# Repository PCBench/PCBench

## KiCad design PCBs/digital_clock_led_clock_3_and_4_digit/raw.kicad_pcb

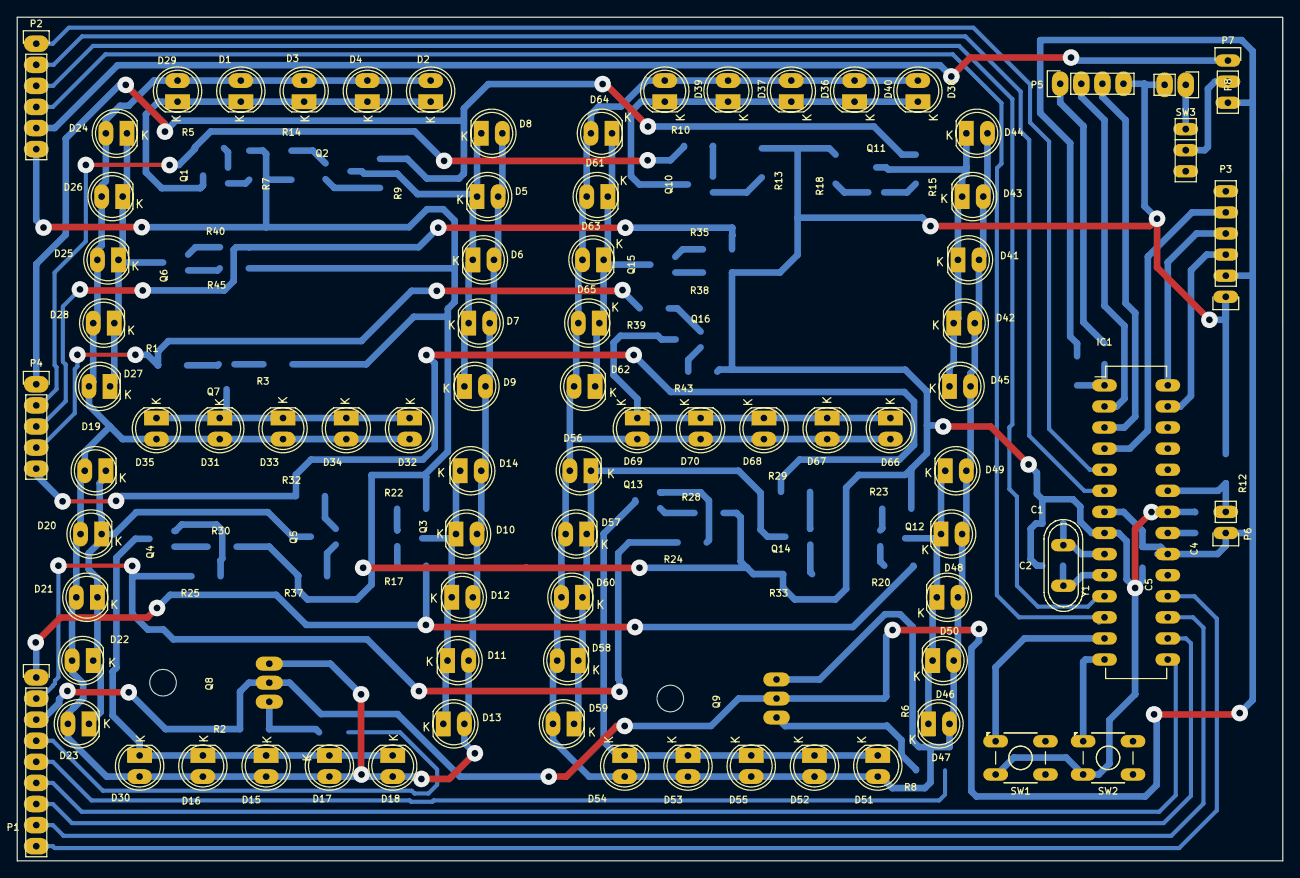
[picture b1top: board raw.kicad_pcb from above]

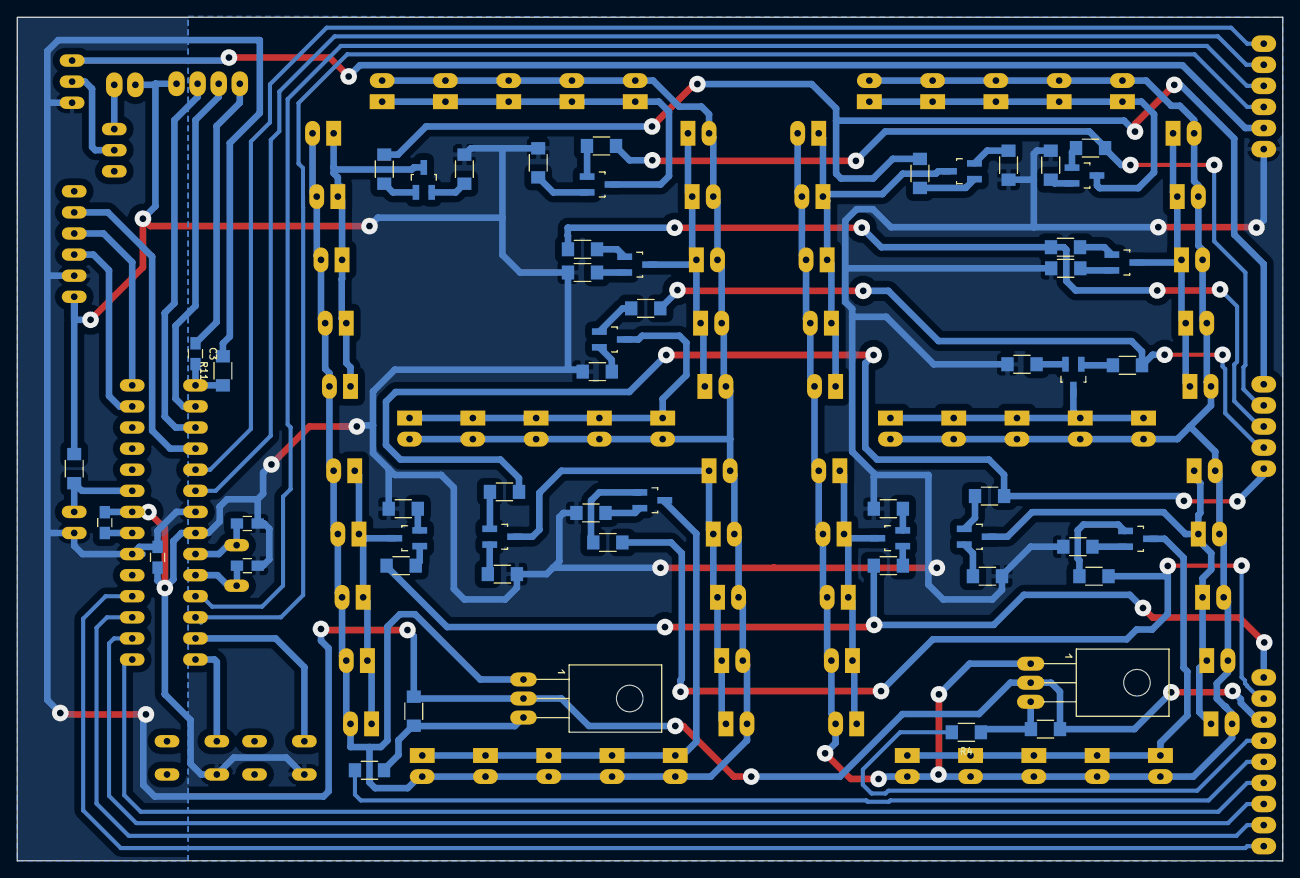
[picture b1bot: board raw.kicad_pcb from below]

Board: 2 copper layers, 152.4 x 101.6 mm, 138 parts (55 on the bottom side), 81 nets.

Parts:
C1, C2: 22P; C_0805_HandSoldering
C3, C4, C5: .1u; C_0805_HandSoldering
D1, D2, D3, D4, D15, D16, D17, D18, D29, D36, D37, D38, D39, D41, D42, D43, D44, D46, D47, D48, D49, D51, D52, D53, D54, D56, D57, D58, D59, D61, D62, D63, D64, D66, D67, D68, D69: D1_A; LED-5MM
D5, D6, D7, D8, D9, D10, D11, D12, D13, D14, D19, D20, D21, D22, D23, D24, D25, D26, D27, D28, D30, D31, D32, D33, D34, D35, D40, D45, D50, D55, D60, D65, D70: D1_B; LED-5MM
IC1: ATMEGA328P-P; DIP-28_W7.62mm_LongPads
P1: BOT_PINS; Pin_Header_Straight_1x09
P2: TOP_PINS; Pin_Header_Straight_1x06
P3: DS3231; Pin_Header_Straight_1x06
P4: CONN_01X05; Pin_Header_Straight_1x05
P5: ICSP; Pin_Header_Straight_1x04
P6: LDR; Pin_Header_Straight_1x02
P7: PWR_SEL; Pin_Header_Straight_1x03
P8: PWR_IN; Pin_Header_Straight_1x02
Q1, Q2, Q3, Q4, Q5, Q6, Q7, Q10, Q11, Q12, Q13, Q14, Q15, Q16: MMBT3904; SOT-23_Handsoldering
Q8, Q9: BD140; SOT126_SOT32_Housing_Horizontal
R1, R5, R9, R10, R15, R17, R20, R24, R25, R29, R32, R35, R39, R40: 560; R_1206_HandSoldering
R2, R6: 0; R_1206_HandSoldering
R3, R7, R13, R14, R18, R22, R23, R28, R30, R33, R37, R38, R43, R45: 68; R_1206_HandSoldering
R4, R8: 220; R_1206_HandSoldering
R11: 1K; R_1206_HandSoldering
R12: 10K; R_1206_HandSoldering
SW1: MENU; SW_TH_Tactile_Omron_B3F-10xx
SW2: UP; SW_TH_Tactile_Omron_B3F-10xx
SW3: Switch_SPDT_x2; SW_Micro_SPST
Y1: 16MHZ; Crystal_HC49-U_Vertical

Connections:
+5V: C5.2, IC1.7, IC1.20, P1.3, P3.2, P6.1, P7.3, Q8.2, Q9.2, R2.2, R6.2, R11.2
/D3_IN: P1.4, R4.2
/D4_IN: P1.5, R8.2
/SEG_A: P4.2, R5.2, R10.2
/SEG_B: P4.1, R9.2, R15.2
/SEG_C: P1.1, R17.2, R20.2
/SEG_D: P1.2, R24.2, R25.2
/SEG_E: P4.5, R29.2, R32.2
/SEG_F: P4.3, R35.2, R40.2
/SEG_G: P4.4, R1.2, R39.2
BCD_A: IC1.12, P2.4
BCD_B: IC1.5, P2.1
BCD_C: IC1.6, P2.2
BCD_D: IC1.11, P2.3
DIG_0: IC1.18, P1.9
DIG_1: IC1.17, P1.8
DIG_2: IC1.16, P1.7
GND: C1.2, C2.2, C4.2, C5.1, IC1.8, IC1.22, P2.6, P3.1, P5.4, P8.2, R3.2, R7.2, R12.2, R13.2, R14.2, R18.2, R22.2, R23.2, R28.2, R30.2, R33.2, R37.2, R38.2, R43.2, R45.2, SW1.2, SW2.2
KEY_MENU: IC1.14, SW2.1
KEY_UP: IC1.13, SW1.1
LDR: IC1.23, P6.2, R12.1
unnamed: C4.1, IC1.21
unnamed: D1.1, D2.1, D3.1, D4.1, D29.1, Q1.3
unnamed: D1.2, D2.2, D3.2, D4.2, D5.2, D6.2, D7.2, D8.2, D9.2, D10.2, D11.2, D12.2, D13.2, D14.2, D15.2, D16.2, D17.2, D18.2, D19.2, D20.2, D21.2, D22.2, D23.2, D24.2, D25.2, D26.2, D27.2, D28.2, D29.2, D30.2, D31.2, D32.2, D33.2, D34.2, D35.2, Q8.1
unnamed: D5.1, D6.1, D7.1, D8.1, D9.1, Q2.3
unnamed: D10.1, D11.1, D12.1, D13.1, D14.1, Q3.3
unnamed: D15.1, D16.1, D17.1, D18.1, D30.1, Q4.3
unnamed: D19.1, D20.1, D21.1, D22.1, D23.1, Q5.3
unnamed: D24.1, D25.1, D26.1, D27.1, D28.1, Q6.3
unnamed: D31.1, D32.1, D33.1, D34.1, D35.1, Q7.3
unnamed: D36.1, D37.1, D38.1, D39.1, D40.1, Q10.3
unnamed: D36.2, D37.2, D38.2, D39.2, D40.2, D41.2, D42.2, D43.2, D44.2, D45.2, D46.2, D47.2, D48.2, D49.2, D50.2, D51.2, D52.2, D53.2, D54.2, D55.2, D56.2, D57.2, D58.2, D59.2, D60.2, D61.2, D62.2, D63.2, D64.2, D65.2, D66.2, D67.2, D68.2, D69.2, D70.2, Q9.1
unnamed: D41.1, D42.1, D43.1, D44.1, D45.1, Q11.3
unnamed: D46.1, D47.1, D48.1, D49.1, D50.1, Q12.3
unnamed: D51.1, D52.1, D53.1, D54.1, D55.1, Q13.3
unnamed: D56.1, D57.1, D58.1, D59.1, D60.1, Q14.3
unnamed: D61.1, D62.1, D63.1, D64.1, D65.1, Q15.3
unnamed: D66.1, D67.1, D68.1, D69.1, D70.1, Q16.3
unnamed: Q1.1, R5.1
unnamed: Q1.2, R7.1
unnamed: Q2.1, R9.1
unnamed: Q2.2, R14.1
unnamed: Q3.1, R17.1
unnamed: Q3.2, R22.1
unnamed: Q4.1, R25.1
unnamed: Q4.2, R30.1
unnamed: Q5.1, R32.1
unnamed: Q5.2, R37.1
unnamed: Q6.1, R40.1
unnamed: Q6.2, R45.1
unnamed: Q7.1, R1.1
unnamed: Q7.2, R3.1
unnamed: Q8.3, R2.1, R4.1
unnamed: Q9.3, R6.1, R8.1
unnamed: Q10.1, R10.1
unnamed: Q10.2, R13.1
unnamed: Q11.1, R15.1
unnamed: Q11.2, R18.1
unnamed: Q12.1, R20.1
unnamed: Q12.2, R23.1
unnamed: Q13.1, R24.1
unnamed: Q13.2, R28.1
unnamed: Q14.1, R29.1
unnamed: Q14.2, R33.1
unnamed: Q15.1, R35.1
unnamed: Q15.2, R38.1
unnamed: Q16.1, R39.1
unnamed: Q16.2, R43.1
OSC1: C1.1, IC1.9, Y1.1
OSC2: C2.1, IC1.10, Y1.2
PWM: IC1.15, P1.6
RST: C3.1, P5.1
RX: IC1.2, P5.2
SCL: IC1.28, P3.4
SDA: IC1.27, P3.3
SQW: IC1.4, P3.5
TX: IC1.3, P5.3
VIN: P2.5, P7.1
VSUP: P8.1, SW3.1
VSUPPLY: P7.2, SW3.2
~RESET: C3.2, IC1.1, R11.1

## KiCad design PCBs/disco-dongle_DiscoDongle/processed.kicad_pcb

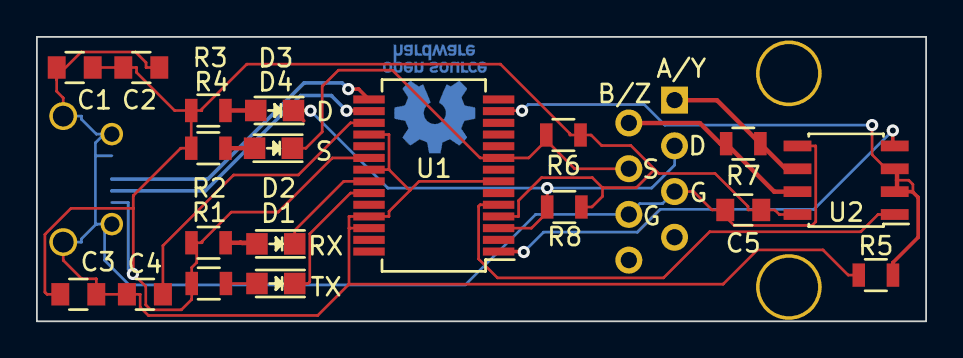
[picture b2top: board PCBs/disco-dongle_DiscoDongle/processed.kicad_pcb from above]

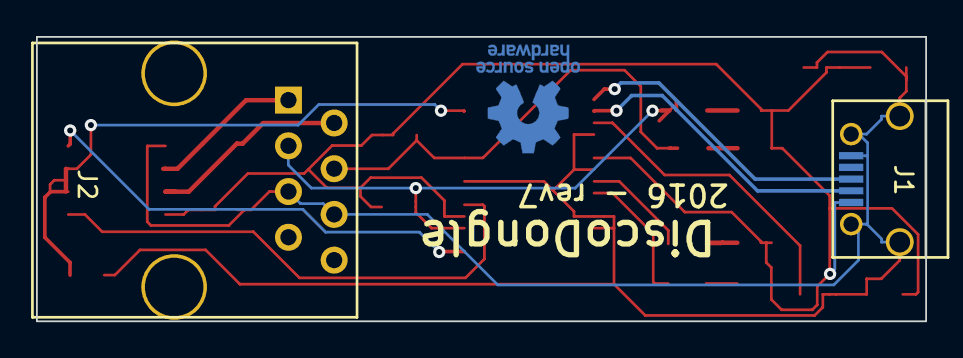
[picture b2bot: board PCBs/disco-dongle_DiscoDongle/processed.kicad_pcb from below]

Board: 2 copper layers, 49.4 x 15.8 mm, 21 parts (2 on the bottom side), 18 nets.

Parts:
C1, C4, C5: 100nF; C_0805
C2: 4.7uF; C_0805
C3: 10nF; C_0805
D1: TX; LED_0805
D2: RX; LED_0805
D3: Daisy; LED_0805
D4: Signal; LED_0805
J1: USB_B_Micro; USB_Micro-B
J2: RJ45; RJ45_8
R1, R2, R3, R4: 200; R_0805
R5, R6, R8: 20k; R_0805
R7: 120; R_0805
U1: FT232RL; SSOP-28_5.3x10.2mm_Pitch0.65mm
U2: ISL81487E; SOIC-8_3.9x4.9mm_Pitch1.27mm

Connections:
+5V: C1.1, C2.1, C3.1, C5.1, J1.1, R1.1, R2.1, R3.1, R4.1, R6.1, R8.1, U1.4, U1.20, U2.8
Daisy: D3.1, J2.3, R8.2, U1.3
GND: C1.2, C2.2, C3.2, C4.2, C5.2, J1.5, J1.6, J2.5, J2.6, R5.2, U1.7, U1.18, U1.21, U1.25, U1.26, U2.5
unnamed: C4.1, U1.17
unnamed: D1.2, R1.2
unnamed: D2.2, R2.2
unnamed: D3.2, R3.2
unnamed: D4.2, R4.2
unnamed: J1.2, U1.16
unnamed: J1.3, U1.15
unnamed: J2.1, R7.2, U2.6
unnamed: J2.2, R7.1, U2.7
unnamed: R5.1, U1.13, U2.2, U2.3
unnamed: U1.1, U2.4
unnamed: U1.5, U2.1
RXLED: D2.1, U1.22
Signal: D4.1, J2.4, R6.2, U1.9
TXLED: D1.1, U1.23

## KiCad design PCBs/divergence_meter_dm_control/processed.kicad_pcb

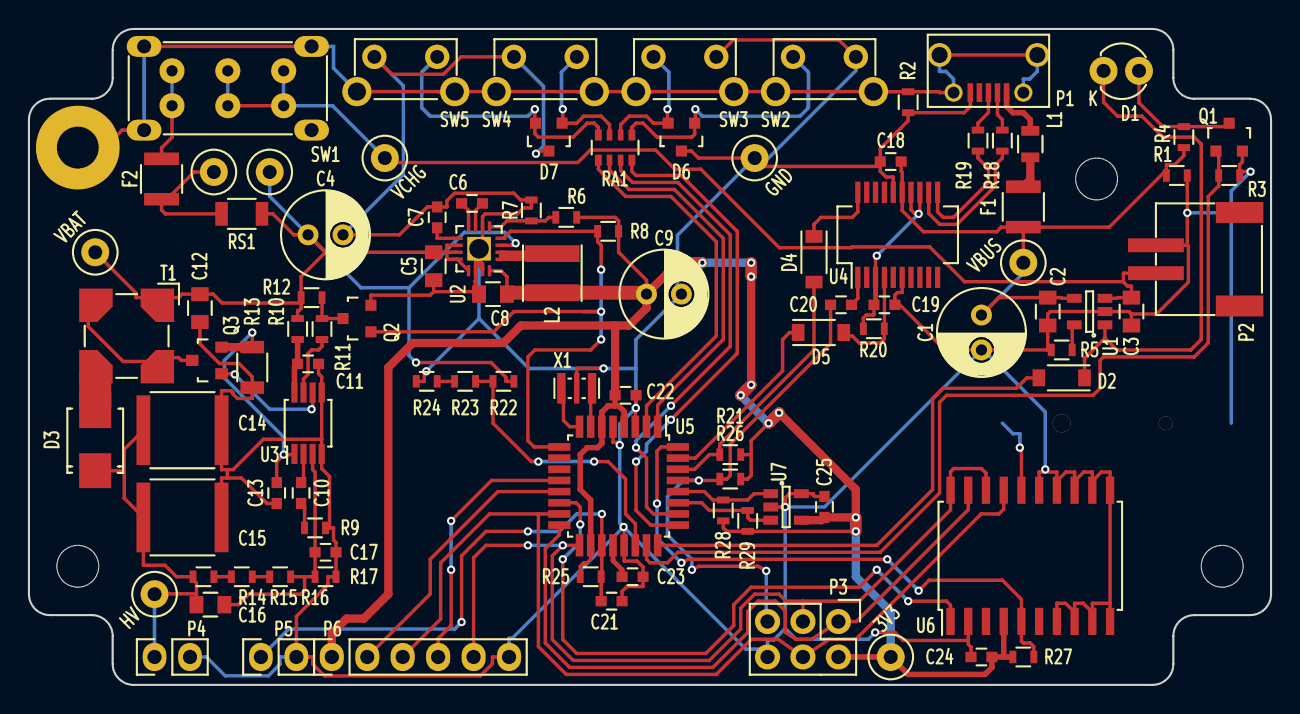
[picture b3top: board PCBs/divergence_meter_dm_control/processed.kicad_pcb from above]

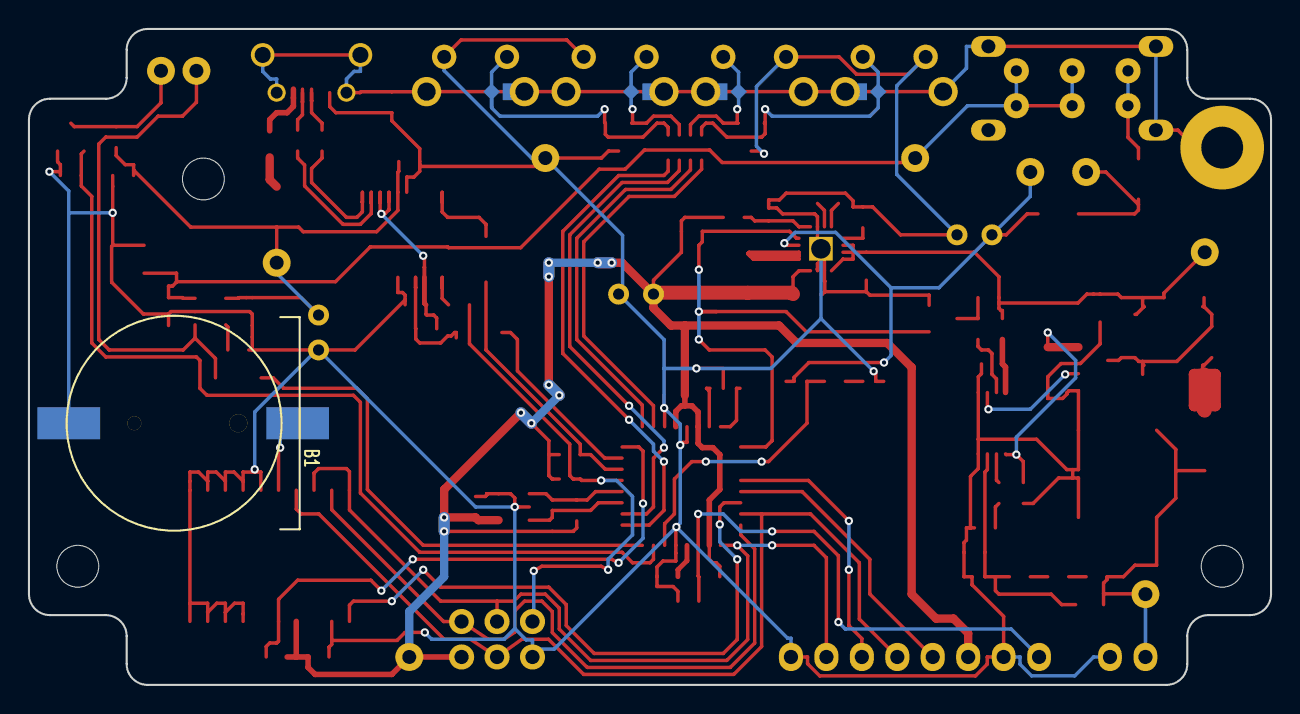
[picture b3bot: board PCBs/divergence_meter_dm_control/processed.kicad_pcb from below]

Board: 2 copper layers, 89.0 x 47.0 mm, 103 parts (5 on the bottom side), 69 nets.

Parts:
B1: Battery; Battery_CR1220
C1, C4, C9: 47u; C_Radial_D6.3_L11.2_P2.5
C2, C3: 4.7u; C_0805
C5, C8, C12: 22u; C_0805
C6, C7, C13, C17: 0.01u; C_0603
C10, C11, C18, C19, C20, C22, C23, C24, C25: 0.1u; C_0603
C14, C15: 1u; C_2220
C16: 100p; C_0805
C21: 1u; C_0603
D1: CHG; LED-3MM
D2, D4, D5: D_Small; SOD-123
D3: STPS4S200; SMB_Standard
D6, D7: MMBZ9V1ALT1G; SOT-23
F1, F2: 1.1A; R_1210
G1, G2, G3, G4: Jumper_NO_Small; SparkGap_0.2mm
L1: Ferrite; R_0805
L2: 1uH; Inductor_Taiyo-Yuden_NR-40xx
P1: USB_OTG; USB_Micro-B
P2: LiPo; Conn_S2B-PH-SM4-TB
P3: ISP; Pin_Header_Straight_2x03
P4: HV; Pin_Header_Straight_1x02
P5: OPTO; Pin_Header_Straight_1x02
P6: DATA; Pin_Header_Straight_1x06
Q1, Q2: 2N7002; SOT-23
Q3: RSR030N06TL; SOT-23
R1, R2, R16: 1M; R_0603
R3, R6: 470k; R_0603
R4, R9, R20, R21: 1k; R_0603
R5: 2k; R_0603
R7, R11: 150k; R_0603
R8, R22, R23, R24: 100k; R_0603
R10: 20; R_0603
R12, R26: 10k; R_0603
R13: 0.1; R_1206
R14: 24k; R_0603
R15: 820k; R_0603
R17: 13k; R_0603
R18, R19: 27; R_0603
R25: 47k; R_0603
R27, R28, R29: 4.7k; R_0603
RA1: 100; R_Array_Convex_4x0603
RS1: 0.01; R_1206
SW1: PWR; PINHEAD1-3
SW2, SW3, SW4, SW5: Push; SW_Tactile_SPST_Angled
T1: LPR6235; Transformer_LPR6235
TP1: VBUS; Test_1
TP2: VCHG; Test_1
TP3: VBAT; Test_1
TP4: 3.3V; Test_1
TP5: GND; Test_1
TP6: 170V; Test_1
TP7: RS1A; Test_1
TP8: RS1B; Test_1
U1: MCP73831; SOT-23-5
U2: TLV62090; QFN-16-1EP_3x3mm_Pitch0.5mm
U3: LM3478; MSOP-8_3x3mm_Pitch0.65mm
U4: FT231XS; SSOP-20_4.0x8.5mm_Pitch0.635mm
U5: ATMEGA328P-A; TQFP-32_7x7mm_Pitch0.8mm
U6: DS3234; SOIC-20W_7.5x12.8mm_Pitch1.27mm
U7: 24AA01T-I/OT; SOT-23-5
X1: 8MHz; Ceralock_CSTCE-G

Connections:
+3V3: C8.1, C9.1, C22.1, C24.1, C25.2, L2.2, P3.2, P6.1, R6.1, R8.1, R21.1, R25.1, R26.1, R27.1, R28.1, R29.1, TP4.1, U2.16, U5.4, U5.6, U5.18, U6.4, U7.4
/APWM: P6.2, U5.13
/AVR_RST: C20.1, P3.5, R26.2, U5.29
/CHASSIS: G1.2, G2.2, G3.2, G4.2, P1.6, R2.1, SW1.4, SW2.3, SW2.4, SW3.3, SW3.4, SW4.3, SW4.4, SW5.3, SW5.4
/CHG_LED: Q1.1, R3.1, U5.23
/CHG_STAT: D2.2, U5.24
/DS_SS: U5.14, U6.1
/FB: C16.2, C17.1, R16.2, R17.1, U3.3
/FT->AVR: D4.2, R21.2, U5.30
/FT<-AVR: D5.1, U5.31
/ISEN: C13.1, Q3.2, R13.1, U3.1
/MISO: P3.1, U5.16, U6.19
/MOSI: P3.4, P6.3, U5.15, U6.17
/OPTO: C21.1, P5.1, R25.2, U5.19
/PG: Q2.1, R8.2, U2.4, U5.9
/RCLK: P6.4, U5.12
/SCK: P3.3, P6.5, U5.17, U6.18, U6.20
/SCL: R28.2, U5.28, U7.1
/SDA: R29.2, U5.27, U7.3
/SQW: R27.2, U5.32, U6.5
/SW0: RA1.8, U5.25
/SW1: RA1.7, U5.26
/SW2: RA1.6, U5.1
/SW3: RA1.5, U5.2
/VBAT: C4.1, C5.1, C12.1, R10.1, R12.2, R22.1, RS1.2, T1.1, TP3.1, TP8.1, U2.3, U2.10, U2.11, U2.12, U2.13
/VBUS: C1.1, C2.1, C18.1, F1.2, R1.1, R4.1, TP1.1, U1.4, U4.15
/VCHG: C3.1, P2.1, SW1.1, SW1.2, TP2.1, U1.3
GND: B1.2, C1.2, C2.2, C3.2, C4.2, C5.2, C7.2, C8.2, C9.2, C11.2, C12.2, C13.2, C14.2, C15.2, C17.2, C18.2, C19.2, C21.2, C22.2, C23.2, C24.2, C25.1, D6.3, D7.3, P1.5, P2.2, P3.6, P4.2, P5.2, P6.6, Q1.2, Q2.2, R1.2, R2.2, R3.2, R5.2, R7.2, R9.2, R13.2, R17.2, R24.2, SW2.2, SW3.2, SW4.1, SW5.1, TP5.1, U1.2, U2.6, U2.14, U2.15, U3.4, U3.5, U4.6, U4.16, U5.3, U5.5, U5.21, U6.2, U6.7, U6.8, U6.9, U6.10, U6.11, U6.12, U6.13, U6.14, U6.15, U7.2, U7.5, X1.3
HT: C14.1, C15.1, C16.1, D3.1, P4.1, R14.1, TP6.1
unnamed: B1.1, U6.16
unnamed: C6.1, U2.8
unnamed: C6.2, U2.7
unnamed: C7.1, U2.9
unnamed: C10.1, U3.2
unnamed: C10.2, R9.1
unnamed: C11.1, R10.2, U3.8
unnamed: C19.1, R20.1, U4.3, U4.13, U4.14
unnamed: C20.2, U4.1
unnamed: C23.1, U5.20
unnamed: D1.1, D2.1, U1.1
unnamed: D1.2, Q1.3, R4.2
unnamed: D3.2, T1.3
unnamed: D4.1, U4.20
unnamed: D5.2, R20.2, U4.4
unnamed: D6.1, G1.1, RA1.1, SW2.1
unnamed: D6.2, G2.1, RA1.2, SW3.1
unnamed: D7.1, G3.1, RA1.3, SW4.2
unnamed: D7.2, G4.1, RA1.4, SW5.2
unnamed: F1.1, L1.2
unnamed: F2.1, SW1.3
unnamed: F2.2, RS1.1, TP7.1
unnamed: L1.1, P1.1
unnamed: L2.1, U2.1, U2.2
unnamed: P1.2, R18.1
unnamed: P1.3, R19.1
unnamed: Q2.3, R11.2, R12.1
unnamed: Q3.1, U3.6
unnamed: Q3.3, T1.2, T1.4
unnamed: R5.1, U1.5
unnamed: R6.2, R7.1, U2.5
unnamed: R11.1, U3.7
unnamed: R14.2, R15.1
unnamed: R15.2, R16.1
unnamed: R18.2, U4.12
unnamed: R19.2, U4.11
unnamed: R22.2, R23.1, U5.22
unnamed: R23.2, R24.1
unnamed: U5.7, X1.2
unnamed: U5.8, X1.1

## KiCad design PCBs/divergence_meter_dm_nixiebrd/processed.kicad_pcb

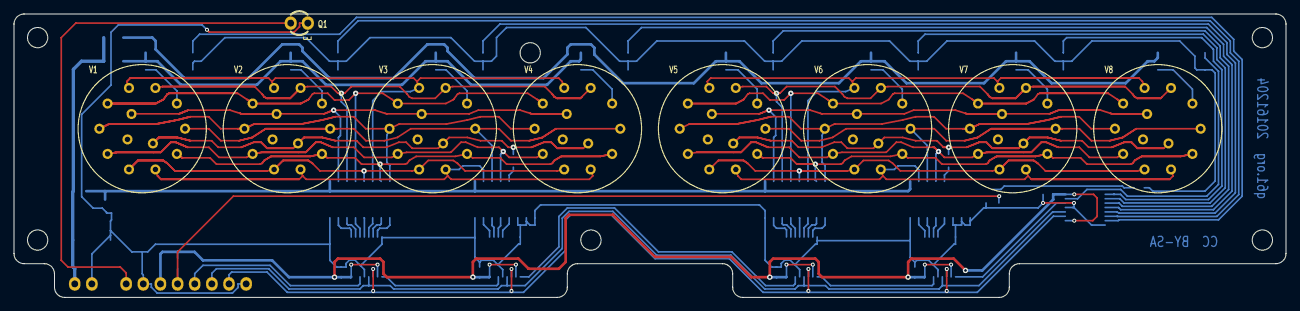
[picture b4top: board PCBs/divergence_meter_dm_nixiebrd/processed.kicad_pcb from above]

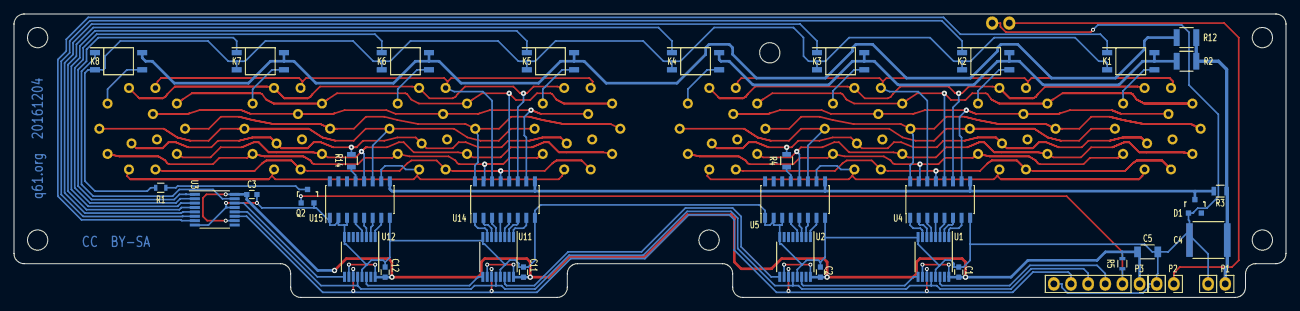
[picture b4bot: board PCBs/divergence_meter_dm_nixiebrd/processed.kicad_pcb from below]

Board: 2 copper layers, 188.5 x 42.0 mm, 45 parts (36 on the bottom side), 79 nets.

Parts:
C1, C2, C3, C11, C12: 0.1u; C_0603
C4: 1u250V; C_2220
C5: 10u; C_1206
D1: 75V_SOT23; SOT-23
K1, K2, K3, K4, K5, K6, K7, K8: TLP188; Optocoupler_SOP6_4
P1: HV; Pin_Header_Straight_1x02
P2: Opto; Pin_Header_Straight_1x02
P3: Signal; Pin_Header_Straight_1x06
Q1: OptTr; OptoTr_TH_3mm_Pitch2.54mm
Q2: 2N7002; SOT-23
R1: 470; R_0603
R2, R12: 3.3k; R_1210
R3: 220k; R_0805
R4, R14: 47k; R_0805
R5: 100k; R_0603
U1, U2, U3, U11, U12: 74HC595; TSSOP-16_4.4x5mm_Pitch0.65mm
U4, U5, U14, U15: SN75468; SOIC-16_3.9x9.9mm_Pitch1.27mm
V1, V2, V3, V4, V5, V6, V7, V8: NL-841; NL-902

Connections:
+3V3: C1.1, C2.1, C3.1, C5.1, C11.1, C12.1, P3.1, R5.1, U1.10, U1.16, U2.10, U2.16, U3.10, U3.16, U11.10, U11.16, U12.10, U12.16
/A1: K1.4, V1.4
/A2: K2.4, V2.4
/A3: K3.4, V3.4
/A4: K4.4, V4.4
/A5: K5.4, V5.4
/A6: K6.4, V6.4
/A7: K7.4, V7.4
/A8: K8.4, V8.4
/ACOM0: K1.6, K2.6, K3.6, K4.6, R2.2
/ACOM1: K5.6, K6.6, K7.6, K8.6, R12.2
/AN1: K1.1, U3.7
/AN2: K2.1, U3.6
/AN3: K3.1, U3.5
/AN4: K4.1, U3.4
/AN5: K5.1, U3.3
/AN6: K6.1, U3.2
/AN7: K7.1, U3.1
/AN8: K8.1, U3.15
/APWM: P3.2, Q2.1, R5.2
/K0: U4.10, V1.13, V2.13, V3.13, V4.13
/K1: U4.11, V1.5, V2.5, V3.5, V4.5
/K2: U4.12, V1.7, V2.7, V3.7, V4.7
/K3: U4.13, V1.10, V2.10, V3.10, V4.10
/K4: U4.14, V1.6, V2.6, V3.6, V4.6
/K5: U4.15, V1.2, V2.2, V3.2, V4.2
/K6: U4.16, V1.8, V2.8, V3.8, V4.8
/K7: U5.10, V1.1, V2.1, V3.1, V4.1
/K8: U5.11, V1.3, V2.3, V3.3, V4.3
/K9: U5.12, V1.9, V2.9, V3.9, V4.9
/K10: U14.10, V5.13, V6.13, V7.13, V8.13
/K11: U14.11, V5.5, V6.5, V7.5, V8.5
/K12: U14.12, V5.7, V6.7, V7.7, V8.7
/K13: U14.13, V5.10, V6.10, V7.10, V8.10
/K14: U14.14, V5.6, V6.6, V7.6, V8.6
/K15: U14.15, V5.2, V6.2, V7.2, V8.2
/K16: U14.16, V5.8, V6.8, V7.8, V8.8
/K17: U15.10, V5.1, V6.1, V7.1, V8.1
/K18: U15.11, V5.3, V6.3, V7.3, V8.3
/K19: U15.12, V5.9, V6.9, V7.9, V8.9
/KDP: R4.2, V1.11, V2.11, V3.11, V4.11
/KDP1: R14.2, V5.11, V6.11, V7.11, V8.11
/KN0: U1.1, U4.7
/KN1: U1.2, U4.6
/KN2: U1.3, U4.5
/KN3: U1.4, U4.4
/KN4: U1.5, U4.3
/KN5: U1.6, U4.2
/KN6: U1.7, U4.1
/KN7: U2.1, U5.7
/KN8: U2.2, U5.6
/KN9: U2.3, U5.5
/KN10: U11.1, U14.7
/KN11: U11.2, U14.6
/KN12: U11.3, U14.5
/KN13: U11.4, U14.4
/KN14: U11.5, U14.3
/KN15: U11.6, U14.2
/KN16: U11.7, U14.1
/KN17: U12.1, U15.7
/KN18: U12.2, U15.6
/KN19: U12.3, U15.5
/KNDP: U2.4, U5.4
/KNDP1: U12.4, U15.4
/RCLK: P3.4, U1.12, U2.12, U3.12, U11.12, U12.12
/SCLK: P3.5, U1.11, U2.11, U3.11, U11.11, U12.11
/SDIN: P3.3, U1.14
/VPREBIAS: D1.3, R3.2, U4.9, U5.9, U14.9, U15.9
GND: C1.2, C2.2, C3.2, C4.2, C5.2, C11.2, C12.2, D1.1, P1.2, P2.2, P3.6, Q1.1, Q2.2, U1.8, U1.13, U2.8, U2.13, U3.8, U3.13, U4.8, U5.1, U5.2, U5.3, U5.8, U11.8, U11.13, U12.8, U12.13, U14.8, U15.1, U15.2, U15.3, U15.8
HT: C4.1, P1.1, R2.1, R3.1, R12.1
unnamed: K1.3, K2.3, K3.3, K4.3, K5.3, K6.3, K7.3, K8.3, R1.2
unnamed: P2.1, Q1.3
unnamed: Q2.3, R1.1
unnamed: R4.1, U5.13
unnamed: R14.1, U15.13
unnamed: U1.9, U2.14
unnamed: U11.9, U12.14
unnamed: U2.9, U11.14
unnamed: U3.14, U12.9

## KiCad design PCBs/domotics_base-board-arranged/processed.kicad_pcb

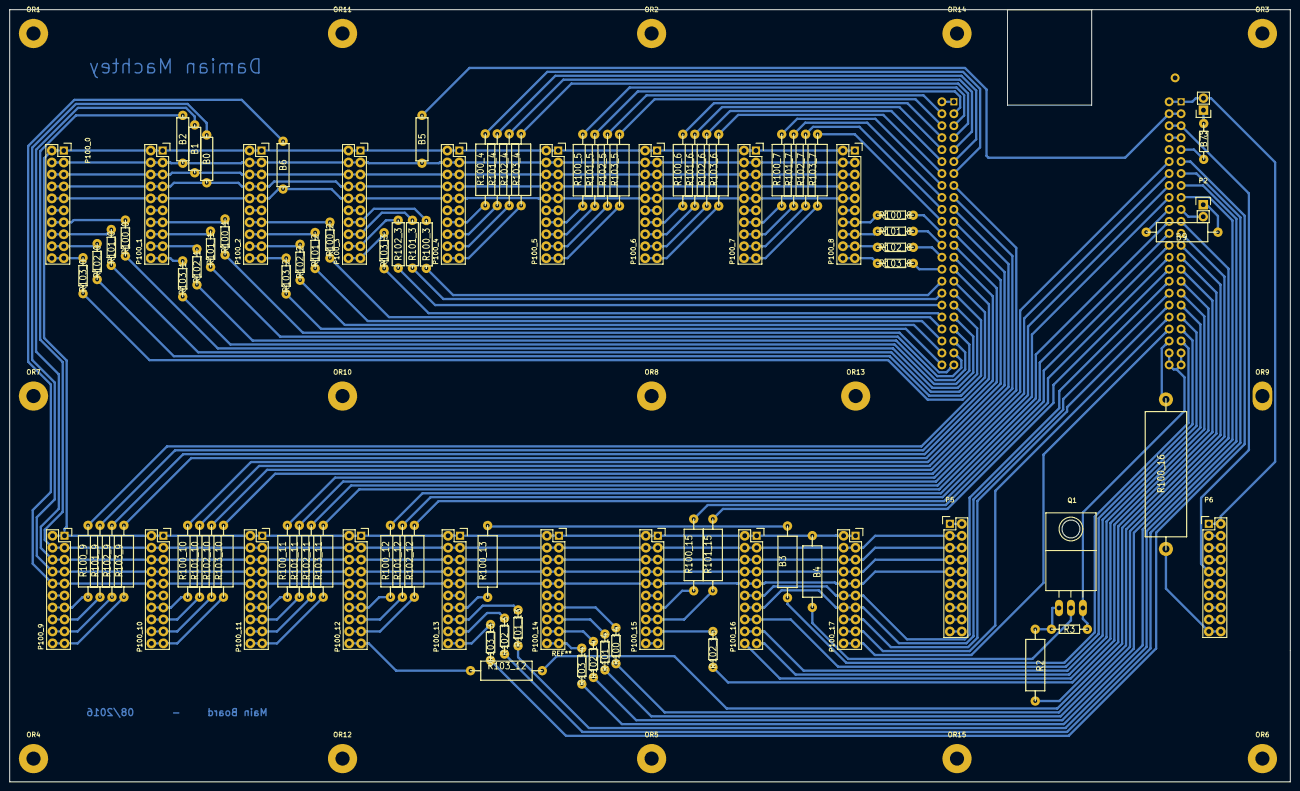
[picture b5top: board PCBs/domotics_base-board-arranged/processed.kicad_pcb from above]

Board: 2 copper layers, 272.0 x 164.0 mm, 114 parts (0 on the bottom side), 191 nets.

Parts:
B0, B1, B2, B5, B6: 0; RC05
B3, B4, B9: 0; RC07
B7: 0; RC03
OR1, OR2, OR3, OR4, OR5, OR6, OR7, OR8, OR9, OR10, OR11, OR12, OR13, OR14, OR15: Fix Hole; SolderWirePad_single_2-5mmDrill
P1: BEAGLEBONE_BLACK; BBB-reversed
P2: I2C; Pin_Header_Straight_1x02
P3: PWR; Pin_Header_Straight_1x02
P5, P6: CONN_02X10; Pin_Header_Straight_2x10
P100_0, P100_1, P100_2, P100_3, P100_4, P100_5, P100_6, P100_7, P100_8, P100_9, P100_10, P100_11, P100_12, P100_13, P100_14, P100_15, P100_16, P100_17: CONN_02X10; Socket_Strip_Straight_2x10
Q1: IRF540N; TO-220_Neutral123_Horizontal_LargePads
R2: 10k; RC07
R3: 47k; RC03
R100_0, R100_1, R100_2, R100_8, R100_14, R101_0, R101_1, R101_2, R101_8, R101_13, R101_14, R102_0, R102_1, R102_2, R102_8, R102_13, R102_14, R102_15, R103_0, R103_1, R103_2, R103_3, R103_8, R103_13, R103_14: 1K; RC03
R100_3, R101_3, R102_3: 1K; RC05
R100_4, R100_5, R100_6, R100_7, R100_9, R100_10, R100_11, R100_12, R100_13, R100_15, R101_4, R101_5, R101_6, R101_7, R101_9, R101_10, R101_11, R101_12, R101_15, R102_4, R102_5, R102_6, R102_7, R102_9, R102_10, R102_11, R102_12, R103_4, R103_5, R103_6, R103_7, R103_9, R103_10, R103_11, R103_12: 1K; RC07
R100_16: 1K; R25x8

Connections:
/12V+: B0.2, P5.7, P5.8, P100_9.7, P100_9.8, P100_10.7, P100_10.8, P100_11.7, P100_11.8, P100_12.7, P100_12.8, P100_13.7, P100_13.8, P100_14.7, P100_14.8, P100_15.7, P100_15.8, P100_16.7, P100_16.8, P100_17.7, P100_17.8
/12V+_TOP: B0.1, P100_0.7, P100_0.8, P100_1.7, P100_1.8, P100_2.7, P100_2.8, P100_3.7, P100_3.8, P100_4.7, P100_4.8, P100_5.7, P100_5.8, P100_6.7, P100_6.8, P100_7.7, P100_7.8, P100_8.7, P100_8.8
/AGND: P1.B34, P100_16.13, P100_16.14, P100_17.13, P100_17.14
/AIN0: P1.B39, P100_16.15, P100_16.16
/AIN1: P1.B40, P100_17.19, P100_17.20
/AIN2: P1.B37, P100_16.17, P100_16.18
/AIN3: P1.B38, P100_17.17, P100_17.18
/AIN4: P1.B33, P100_16.20
/AIN5: P1.B36, P100_17.15, P100_17.16
/AIN6: P1.B35, P100_16.19
/DC_3.3V: B2.2, P5.3, P5.4, P100_9.3, P100_9.4, P100_10.3, P100_10.4, P100_11.3, P100_11.4, P100_12.3, P100_12.4, P100_13.3, P100_13.4, P100_14.3, P100_14.4, P100_15.3, P100_15.4, P100_16.3, P100_16.4, P100_17.3, P100_17.4
/DC_3.3V_TOP: B2.1, B5.1, P100_0.3, P100_0.4, P100_1.3, P100_1.4, P100_2.3, P100_2.4, P100_3.3, P100_3.4, P100_4.3, P100_4.4, P100_5.3, P100_5.4, P100_6.3, P100_6.4, P100_7.3, P100_7.4, P100_8.3, P100_8.4
/DC_3.3Ve: B5.2, P1.B3, P1.B4
/GND: B4.1, P100_0.1, P100_0.2, P100_1.1, P100_1.2, P100_2.1, P100_2.2, P100_3.1, P100_3.2, P100_4.1, P100_4.2, P100_5.1, P100_5.2, P100_6.1, P100_6.2, P100_7.1, P100_7.2, P100_8.1, P100_8.2, P100_9.1, P100_9.2, P100_10.1, P100_10.2, P100_11.1, P100_11.2, P100_12.1, P100_12.2, P100_13.1, P100_13.2, P100_14.1, P100_14.2, P100_15.1, P100_15.2, P100_16.1, P100_16.2, P100_17.1, P100_17.2
/GND1: P1.B1, P1.B2, P3.2, P6.1, P6.2
/GND2: P1.A1, P1.A2
/GND3: P1.B43, P1.B44, P1.B45, P1.B46, Q1.3, R3.1
/GND12V: B1.2, P5.5, P5.6, P100_9.5, P100_9.6, P100_10.5, P100_10.6, P100_11.5, P100_11.6, P100_12.5, P100_12.6, P100_13.5, P100_13.6, P100_14.5, P100_14.6, P100_15.5, P100_15.6, P100_16.5, P100_16.6, P100_17.5, P100_17.6
/GND12V_TOP: B1.1, P100_0.5, P100_0.6, P100_1.5, P100_1.6, P100_2.5, P100_2.6, P100_3.5, P100_3.6, P100_4.5, P100_4.6, P100_5.5, P100_5.6, P100_6.5, P100_6.6, P100_7.5, P100_7.6, P100_8.5, P100_8.6
/GPIO0_2: P1.B22, R100_12.2
/GPIO0_3: P1.B21, R102_14.2
/GPIO0_4: P1.B18, R103_11.2
/GPIO0_5: P1.B17, R103_14.2
/GPIO0_7: P1.B42, R100_16.2
/GPIO0_8: P1.A35, R101_0.2
/GPIO0_9: P1.A33, R102_0.2
/GPIO0_10: P1.A31, R103_0.2
/GPIO0_11: P1.A32, R100_3.2
/GPIO0_14: P1.B26, R102_12.2
/GPIO0_15: P1.B24, R101_12.2
/GPIO0_20: B3.1, P1.B41
/GPIO0_22: P1.A19, R101_10.2
/GPIO0_23: P1.A13, R100_4.2
/GPIO0_26: P1.A14, R103_6.2
/GPIO0_27: P1.A17, R102_10.2
/GPIO0_30: P1.B11, R103_13.2
/GPIO0_31: P1.B13, R102_13.2
/GPIO1_0: P1.A25, R102_9.2
/GPIO1_1: P1.A24, R100_8.2
/GPIO1_2: P1.A5, R100_5.2
/GPIO1_3: P1.A6, R103_5.2
/GPIO1_4: P1.A23, R103_9.2
/GPIO1_5: P1.A22, R103_7.2
/GPIO1_6: P1.A3, R101_5.2
/GPIO1_7: P1.A4, R102_5.2
/GPIO1_12: P1.A12, R102_6.2
/GPIO1_13: P1.A11, R101_4.2
/GPIO1_14: P1.A16, R100_7.2
/GPIO1_15: P1.A15, R103_10.2
/GPIO1_16: P1.B15, R101_13.2
/GPIO1_17: P1.B23, R101_14.2
/GPIO1_18: P1.B14, R101_11.2
/GPIO1_19: P1.B16, R102_11.2
/GPIO1_28: P1.B12, R100_11.2
/GPIO1_29: P1.A26, R101_8.2
/GPIO1_30: P1.A21, R100_10.2
/GPIO1_31: P1.A20, R102_7.2
/GPIO2_1: P1.A18, R101_7.2
/GPIO2_2: P1.A7, R103_4.2
/GPIO2_3: P1.A8, R100_6.2
/GPIO2_4: P1.A10, R101_6.2
/GPIO2_5: P1.A9, R102_4.2
/GPIO2_6: P1.A45, R100_1.2
/GPIO2_7: P1.A46, R103_2.2
/GPIO2_8: P1.A43, R101_1.2
/GPIO2_9: P1.A44, R102_2.2
/GPIO2_10: P1.A41, R102_1.2
/GPIO2_11: P1.A42, R101_2.2
/GPIO2_12: P1.A39, R103_1.2
/GPIO2_13: P1.A40, R100_2.2
/GPIO2_14: P1.A37, R100_0.2
/GPIO2_15: P1.A38, R103_3.2
/GPIO2_16: P1.A36, R102_3.2
/GPIO2_17: P1.A34, R101_3.2
/GPIO2_22: P1.A27, R101_9.2
/GPIO2_23: P1.A29, R100_9.2
/GPIO2_24: P1.A28, R102_8.2
/GPIO2_25: P1.A30, R103_8.2
/GPIO3_14: P1.B31, R102_15.2
/GPIO3_15: P1.B29, R2.2
/GPIO3_16: P1.B30, R101_15.2
/GPIO3_17: P1.B28, R100_15.2
/GPIO3_19: P1.B27, R103_12.2
/GPIO3_21: P1.B25, R100_14.2
/I2C2_SCL: P1.B19, P2.2
/I2C2_SDA: B9.2, P1.B20
/PWR_BUT: B7.2, P1.B9
/SYS_5V: P1.B7, P1.B8
/VADC: P1.B32, P100_16.11, P100_16.12, P100_17.11, P100_17.12
/VDD_5V: P1.B5, P1.B6, P6.9, P6.10
/VDD_5V_DOWN: B6.2, P5.9, P5.10, P100_9.9, P100_9.10, P100_10.9, P100_10.10, P100_11.9, P100_11.10, P100_12.9, P100_12.10, P100_13.9, P100_13.10, P100_14.9, P100_14.10, P100_15.9, P100_15.10, P100_16.9, P100_16.10, P100_17.9, P100_17.10
/VDD_5V_TOP: B6.1, P100_0.9, P100_0.10, P100_1.9, P100_1.10, P100_2.9, P100_2.10, P100_3.9, P100_3.10, P100_4.9, P100_4.10, P100_5.9, P100_5.10, P100_6.9, P100_6.10, P100_7.9, P100_7.10, P100_8.9, P100_8.10
unnamed: B3.2, R100_13.2
unnamed: B4.2, Q1.2
unnamed: B7.1, P3.1
unnamed: B9.1, P2.1
unnamed: P5.1, P5.2
unnamed: P5.11, P5.12
unnamed: P5.13, P5.14
unnamed: P5.15, P5.16
unnamed: P5.17, P5.18
unnamed: P5.19, P5.20
unnamed: P6.3, P6.4
unnamed: P6.5, P6.6
unnamed: P6.7, P6.8
unnamed: P6.11, P6.12
unnamed: P6.13, P6.14
unnamed: P6.15, P6.16
unnamed: P6.17, P6.18
unnamed: P6.19, P6.20, R100_16.1
unnamed: P100_0.11, P100_0.12
unnamed: P100_0.13, P100_0.14, R100_0.1
unnamed: P100_0.15, P100_0.16, R101_0.1
unnamed: P100_0.17, P100_0.18, R102_0.1
unnamed: P100_0.19, P100_0.20, R103_0.1
unnamed: P100_1.11, P100_1.12
unnamed: P100_1.13, P100_1.14, R100_1.1
unnamed: P100_1.15, P100_1.16, R101_1.1
unnamed: P100_1.17, P100_1.18, R102_1.1
unnamed: P100_1.19, P100_1.20, R103_1.1
unnamed: P100_2.11, P100_2.12
unnamed: P100_2.13, P100_2.14, R100_2.1
unnamed: P100_2.15, P100_2.16, R101_2.1
unnamed: P100_2.17, P100_2.18, R102_2.1
unnamed: P100_2.19, P100_2.20, R103_2.1
unnamed: P100_3.11, P100_3.12
unnamed: P100_3.13, P100_3.14, R100_3.1
unnamed: P100_3.15, P100_3.16, R101_3.1
unnamed: P100_3.17, P100_3.18, R102_3.1
unnamed: P100_3.19, P100_3.20, R103_3.1
unnamed: P100_4.11, P100_4.12
unnamed: P100_4.13, P100_4.14, R100_4.1
unnamed: P100_4.15, P100_4.16, R101_4.1
unnamed: P100_4.17, P100_4.18, R102_4.1
unnamed: P100_4.19, P100_4.20, R103_4.1
unnamed: P100_5.11, P100_5.12
unnamed: P100_5.13, P100_5.14, R100_5.1
unnamed: P100_5.15, P100_5.16, R101_5.1
unnamed: P100_5.17, P100_5.18, R102_5.1
unnamed: P100_5.19, P100_5.20, R103_5.1
unnamed: P100_6.11, P100_6.12
unnamed: P100_6.13, P100_6.14, R100_6.1
unnamed: P100_6.15, P100_6.16, R101_6.1
unnamed: P100_6.17, P100_6.18, R102_6.1
unnamed: P100_6.19, P100_6.20, R103_6.1
unnamed: P100_7.11, P100_7.12
unnamed: P100_7.13, P100_7.14, R100_7.1
unnamed: P100_7.15, P100_7.16, R101_7.1
unnamed: P100_7.17, P100_7.18, R102_7.1
unnamed: P100_7.19, P100_7.20, R103_7.1
unnamed: P100_8.11, P100_8.12
unnamed: P100_8.13, P100_8.14, R100_8.1
unnamed: P100_8.15, P100_8.16, R101_8.1
unnamed: P100_8.17, P100_8.18, R102_8.1
unnamed: P100_8.19, P100_8.20, R103_8.1
unnamed: P100_9.11, P100_9.12
unnamed: P100_9.13, P100_9.14, R100_9.1
unnamed: P100_9.15, P100_9.16, R101_9.1
unnamed: P100_9.17, P100_9.18, R102_9.1
unnamed: P100_9.19, P100_9.20, R103_9.1
unnamed: P100_10.11, P100_10.12
unnamed: P100_10.13, P100_10.14, R100_10.1
unnamed: P100_10.15, P100_10.16, R101_10.1
unnamed: P100_10.17, P100_10.18, R102_10.1
unnamed: P100_10.19, P100_10.20, R103_10.1
unnamed: P100_11.11, P100_11.12
unnamed: P100_11.13, P100_11.14, R100_11.1
unnamed: P100_11.15, P100_11.16, R101_11.1
unnamed: P100_11.17, P100_11.18, R102_11.1
unnamed: P100_11.19, P100_11.20, R103_11.1
unnamed: P100_12.11, P100_12.12
unnamed: P100_12.13, P100_12.14, R100_12.1
unnamed: P100_12.15, P100_12.16, R101_12.1
unnamed: P100_12.17, P100_12.18, R102_12.1
unnamed: P100_12.19, P100_12.20, R103_12.1
unnamed: P100_13.11, P100_13.12
unnamed: P100_13.13, P100_13.14, R100_13.1
unnamed: P100_13.15, P100_13.16, R101_13.1
unnamed: P100_13.17, P100_13.18, R102_13.1
unnamed: P100_13.19, P100_13.20, R103_13.1
unnamed: P100_14.11, P100_14.12
unnamed: P100_14.13, P100_14.14, R100_14.1
unnamed: P100_14.15, P100_14.16, R101_14.1
unnamed: P100_14.17, P100_14.18, R102_14.1
unnamed: P100_14.19, P100_14.20, R103_14.1
unnamed: P100_15.11, P100_15.12
unnamed: P100_15.13, P100_15.14, R100_15.1
unnamed: P100_15.15, P100_15.16, R101_15.1
unnamed: P100_15.17, P100_15.18, R102_15.1
unnamed: P100_15.19, P100_15.20
unnamed: Q1.1, R2.1, R3.2

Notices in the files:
PCBs/divergence_meter_dm_control/processed.kicad_pcb:
License: CC BY-SA 4.0 International
This PCB file is licensed under a
Creative Commons Attribution-ShareAlike 4.0 International License.
PCBs/divergence_meter_dm_nixiebrd/processed.kicad_pcb:
This PCB file is licensed under a Creative Commons Attribution-ShareAlike 4.0 International License.
